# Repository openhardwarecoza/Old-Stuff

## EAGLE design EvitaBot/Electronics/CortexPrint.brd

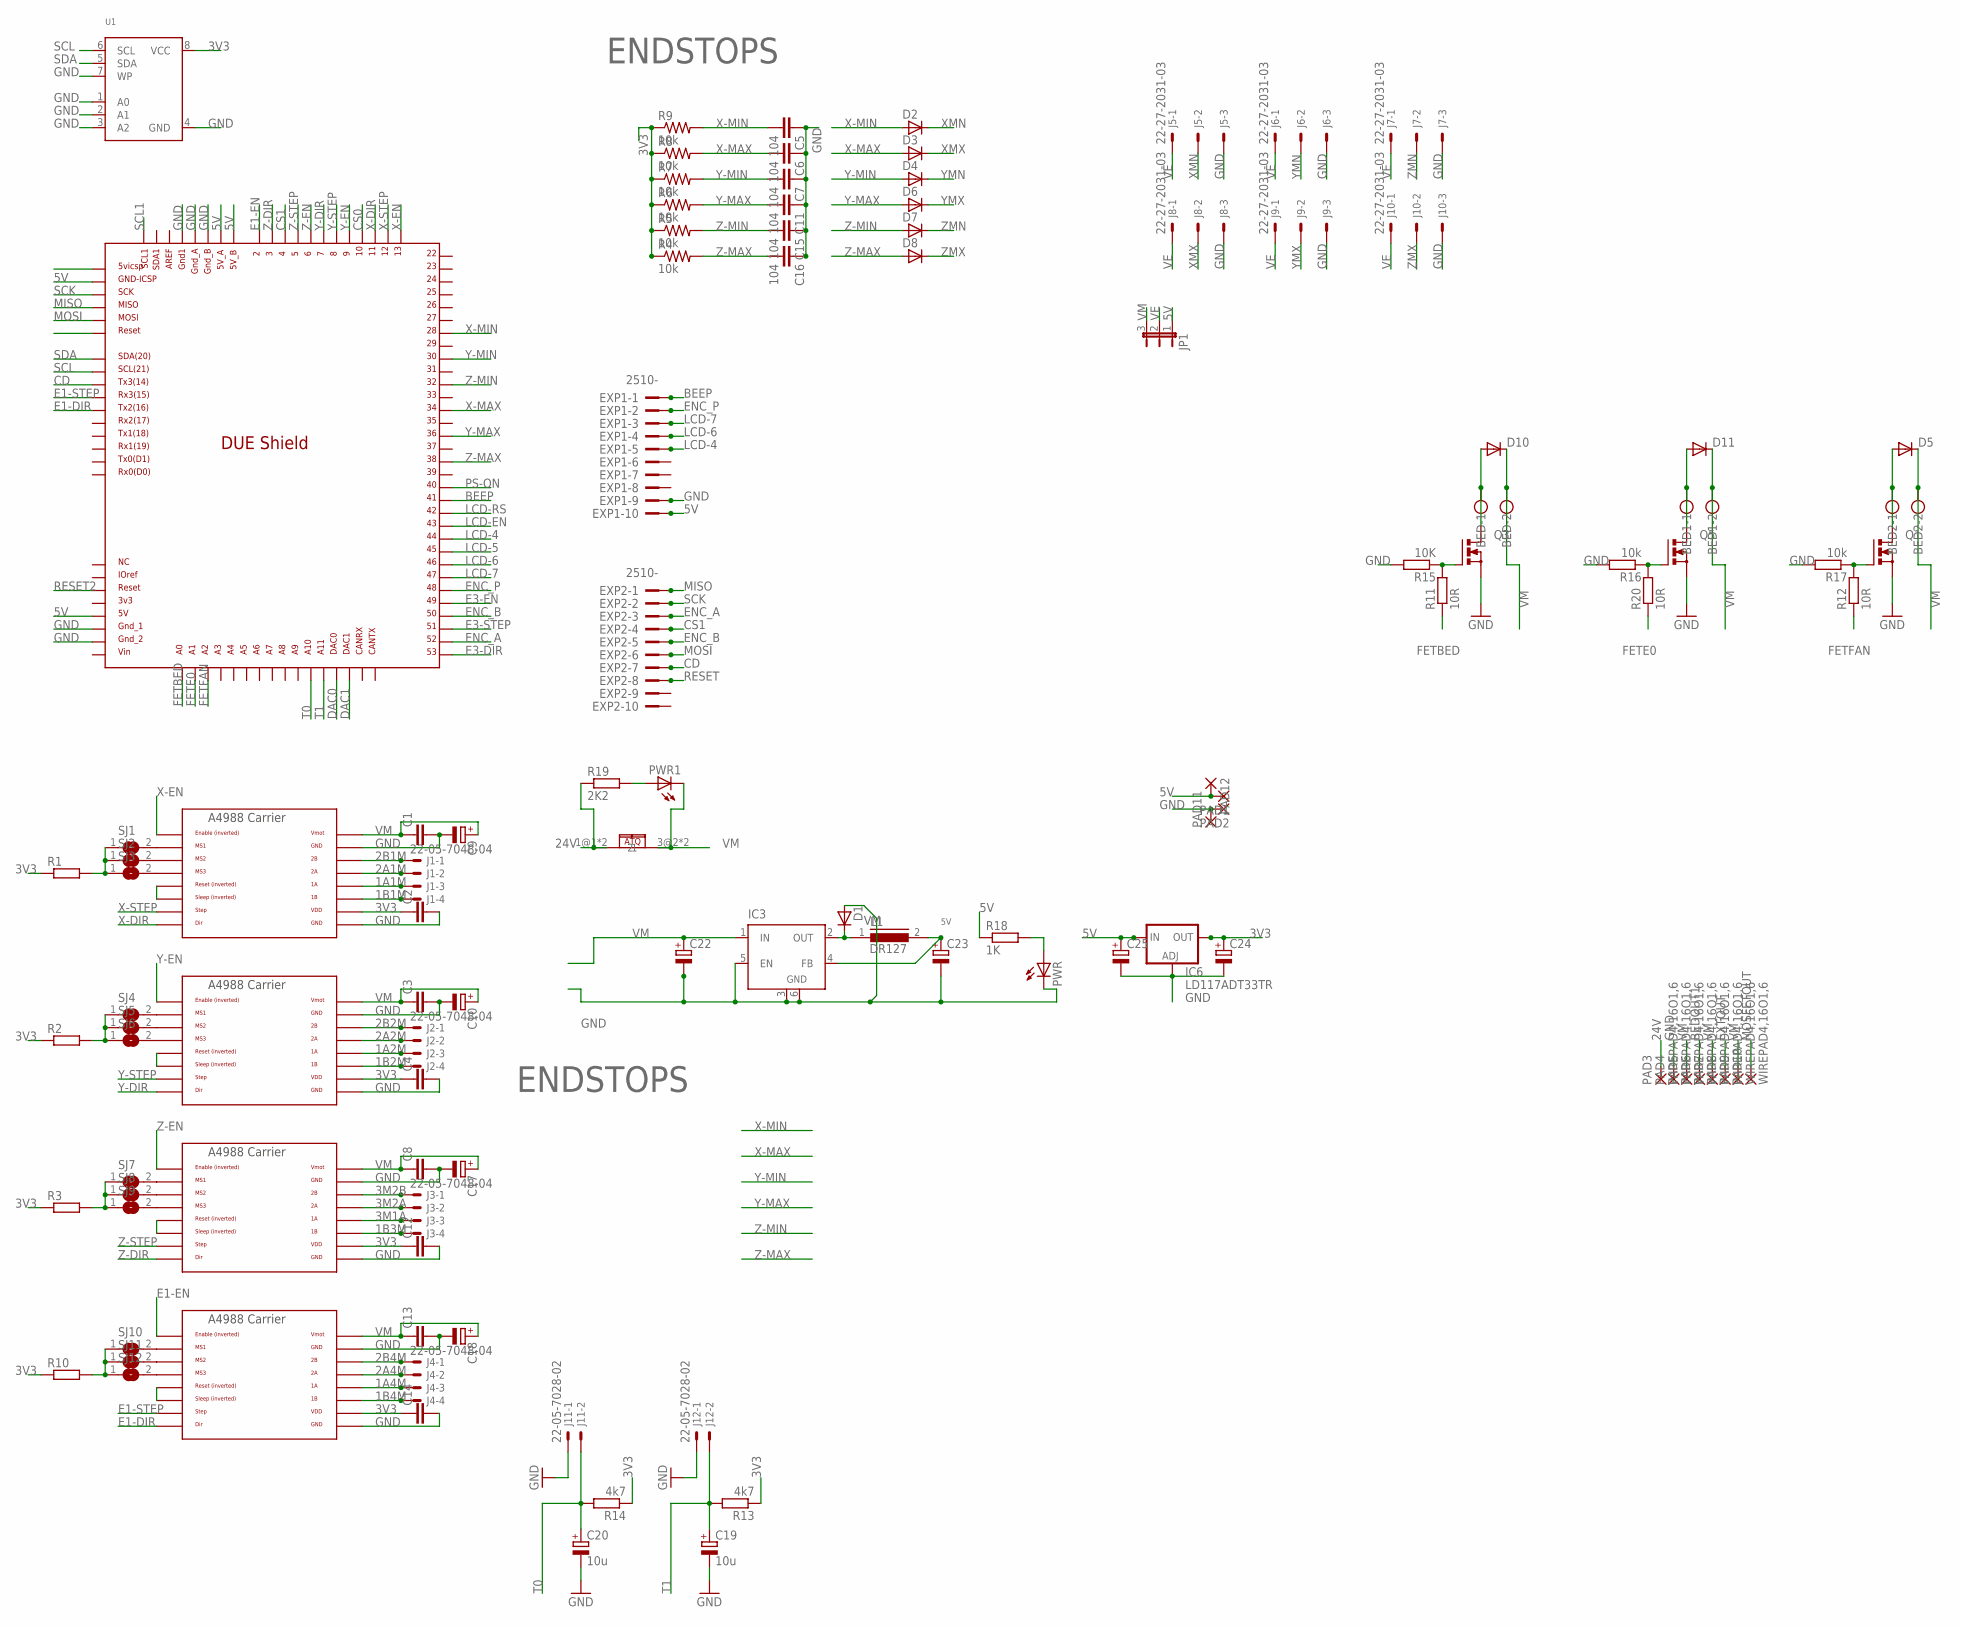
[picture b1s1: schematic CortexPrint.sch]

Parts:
BED, BED1, BED2: W237-102
C1, C2, C3, C4, C8, C12, C13, C14: C-EUC1206; C1206
C5, C6, C7, C11, C15, C16: 104; C1206
C9, C10, C17, C18: CPOL-EUE2,5-6E; E2,5-6E
C19, C20: 10u; SANYO-OSCON_SMD_B6
C22, C23: CPOL-EUE; PANASONIC_E
C24, C25: CPOL-EUD; PANASONIC_D
D1, D2, D3, D4, D6, D7, D8: D-SOD-87; SOD87
D5, D10, D11: DIODESMA-ALT; SMA-DIODE_ALT
EXP1, EXP2: 2510-; PAK100/2500-10
IC3: LM2596S; TO263-5
IC6: LD117ADT33TR; DPACK
J1, J2, J3, J4: 22-05-7048-04; 7395-04
J5, J6, J7, J8, J9, J10: 22-27-2031-03; 6410-03
J11, J12: 22-05-7028-02; 7395-02
JP1: JP2E; JP2
L1: DR127
PAD1, PAD2, PAD11, PAD12: 3,81/1,4
PAD3, PAD4, PAD5, PAD6, PAD7, PAD8, PAD9, PAD10: WIREPAD4,16O1,6; 4,16O1,6
PWR, PWR1: LEDCHIPLED_1206; CHIPLED_1206
Q1, Q3, Q5: PMOSFET_NTO220BV; TO220BV
R1, R3, R10: R-EU_0207/7; 0207/7
R2: R-EU_0204/7; 0204/7
R4, R5, R6, R7, R8, R9, R16, R17: 10k; M1206
R11, R12, R20: 10R; M1206
R13, R14: 4k7; M1206
R15: 10K; M1206
R18: 1K; M1206
R19: 2K2; M1206
SJ1, SJ2, SJ3, SJ4, SJ5, SJ6, SJ7, SJ8, SJ9, SJ10, SJ11, SJ12: SJ
U1: EEPROM_I2C_SOIC8_GENERIC; SOIC8_150MIL
U$1: DUE(NORMAL)
U$2, U$3, U$4, U$5: POLOLU_A4983CARRIER; A4988BREAKOUT
U$7: CQ-121; CQ121

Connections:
1A1M: J1.3, U$2.1A
1A2M: J2.3, U$3.1A
1A4M: J4.3, U$5.1A
1B1M: J1.4, U$2.1B
1B2M: J2.4, U$3.1B
1B3M: J3.4, U$4.1B
1B4M: J4.4, U$5.1B
2A1M: J1.2, U$2.2A
2A2M: J2.2, U$3.2A
2A4M: J4.2, U$5.2A
2B1M: J1.1, U$2.2B
2B2M: J2.1, U$3.2B
2B4M: J4.1, U$5.2B
3M1A: J3.3, U$4.1A
3M2A: J3.2, U$4.2A
3M2B: J3.1, U$4.2B
3V3: C2.1, C4.1, C12.1, C14.1, C24.+, IC6.4 (OUT), R1.1, R2.1, R3.1, R4.1, R5.1, R6.1, R7.1, R8.1, R9.1, R10.1, R13.1, R14.1, U1.8 (VCC), U$2.VDD, U$3.VDD, U$4.VDD, U$5.VDD
5V: C23.+, C25.+, EXP1.10, IC3.4 (FB), IC6.3 (IN), JP1.1, L1.2, PAD1.1, PAD12.1, R18.1, U$1.5V-P (5V), U$1.5V_A, U$1.5V_B, U$1.GND_ICSP
24V: PAD3.1, R19.1, U$7.1@1 (1), U$7.2@1 (1)
BEDOUT1: BED.1, D10.A, PAD6.1, Q3.D
BEEP: EXP1.1, U$1.41
CD: EXP2.7, U$1.TX3
CS0: U$1.10
CS1: EXP2.4, U$1.4
DAC0: U$1.DAC0
DAC1: U$1.DAC1
E1-DIR: U$1.TX2, U$5.DIR
E1-EN: U$1.2, U$5.EN
E1-STEP: U$1.RX3, U$5.STEP
E3-DIR: U$1.53
E3-EN: U$1.49
E3-STEP: U$1.51
ENC_A: EXP2.3, U$1.52
ENC_B: EXP2.5, U$1.50
ENC_P: EXP1.2, U$1.48
EXTOUT: BED1.1, D11.A, PAD8.1, Q5.D
FETBED: R11.1, U$1.A0
FETE0: R20.1, U$1.A1
FETFAN: R12.1, U$1.A2
GND: C1.2, C2.2, C3.2, C4.2, C5.1, C6.1, C7.1, C8.2, C9.-, C10.-, C11.1, C12.2, C13.2, C14.2, C15.1, C16.1, C17.-, C18.-, C19.-, C20.-, C22.-, C23.-, C24.-, C25.-, D1.2 (A), EXP1.9, IC3.3 (GND), IC3.5 (EN), IC3.6 (GND), IC6.1 (ADJ), J5.3, J6.3, J7.3, J8.3, J9.3, J10.3, J11.1, J12.1, PAD2.1, PAD4.1, PAD11.1, PWR.C, Q1.S, Q3.S, Q5.S, R15.2, R16.2, R17.2, U1.1 (A0), U1.2 (A1), U1.3 (A2), U1.4 (GND), U1.7 (WP), U$1.GND1, U$1.GND_1, U$1.GND_2, U$1.GND_A, U$1.GND_B, U$2.GND, U$2.GND@0 (GND), U$3.GND, U$3.GND@0 (GND), U$4.GND, U$4.GND@0 (GND), U$5.GND, U$5.GND@0 (GND)
LCD-4: EXP1.5, U$1.44
LCD-5: U$1.45
LCD-6: EXP1.4, U$1.46
LCD-7: EXP1.3, U$1.47
LCD-EN: U$1.43
LCD-RS: U$1.42
MISO: EXP2.1, U$1.MISO_ICSP
MOSFETOUT: BED2.1, D5.A, PAD10.1, Q1.D
MOSI: EXP2.6, U$1.MOSI_ICSP
unnamed: Q1.G, R12.2, R17.1
unnamed: D1.1 (C), IC3.2 (OUT), L1.1
unnamed: PWR1.A, R19.2
unnamed: U$3.RST, U$3.SLP (SLEEP)
unnamed: SJ4.2, U$3.MS1
unnamed: SJ1.2, U$2.MS1
unnamed: SJ2.2, U$2.MS2
unnamed: SJ3.2, U$2.MS3
unnamed: R1.2, SJ1.1, SJ2.1, SJ3.1
unnamed: SJ5.2, U$3.MS2
unnamed: SJ6.2, U$3.MS3
unnamed: R2.2, SJ4.1, SJ5.1, SJ6.1
unnamed: U$4.RST, U$4.SLP (SLEEP)
unnamed: SJ7.2, U$4.MS1
unnamed: U$2.RST, U$2.SLP (SLEEP)
unnamed: SJ8.2, U$4.MS2
unnamed: SJ9.2, U$4.MS3
unnamed: R3.2, SJ7.1, SJ8.1, SJ9.1
unnamed: U$5.RST, U$5.SLP (SLEEP)
unnamed: SJ10.2, U$5.MS1
unnamed: SJ11.2, U$5.MS2
unnamed: SJ12.2, U$5.MS3
unnamed: R10.2, SJ10.1, SJ11.1, SJ12.1
unnamed: PWR.A, R18.2
unnamed: Q5.G, R16.1, R20.2
unnamed: Q3.G, R11.2, R15.1
PS-ON: U$1.40
RESET: EXP2.8, U$1.RESET_ICSP
RESET2: U$1.RESET
SCK: EXP2.2, U$1.SCK_ICSP
SCL: U1.6 (SCL), U$1.SCL
SCL1: U$1.SCL1
SDA: U1.5 (SDA), U$1.SDA
T0: C20.+, J11.2, R14.2, U$1.A10
T1: C19.+, J12.2, R13.2, U$1.A11
VE: J5.1, J6.1, J7.1, J8.1, J9.1, J10.1, JP1.2
VM: BED.2, BED1.2, BED2.2, C1.1, C3.1, C8.1, C9.+, C10.+, C13.1, C17.+, C18.+, C22.+, D5.C, D10.C, D11.C, IC3.1 (IN), JP1.3, PAD5.1, PAD7.1, PAD9.1, PWR1.C, U$2.VMOT, U$3.VMOT, U$4.VMOT, U$5.VMOT, U$7.3@2 (2), U$7.4@2 (2)
X-DIR: U$1.11, U$2.DIR
X-EN: U$1.13, U$2.EN
X-MAX: C6.2, D3.2 (A), R8.2, U$1.34
X-MIN: C5.2, D2.2 (A), R9.2, U$1.28
X-STEP: U$1.12, U$2.STEP
XMN: D2.1 (C), J5.2
XMX: D3.1 (C), J8.2
Y-DIR: U$1.7, U$3.DIR
Y-EN: U$1.9, U$3.EN
Y-MAX: C11.2, D6.2 (A), R6.2, U$1.36
Y-MIN: C7.2, D4.2 (A), R7.2, U$1.30
Y-STEP: U$1.8, U$3.STEP
YMN: D4.1 (C), J6.2
YMX: D6.1 (C), J9.2
Z-DIR: U$1.3, U$4.DIR
Z-EN: U$1.6, U$4.EN
Z-MAX: C16.2, D8.2 (A), R4.2, U$1.38
Z-MIN: C15.2, D7.2 (A), R5.2, U$1.32
Z-STEP: U$1.5, U$4.STEP
ZMN: D7.1 (C), J7.2
ZMX: D8.1 (C), J10.2

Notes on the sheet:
ENDSTOPS

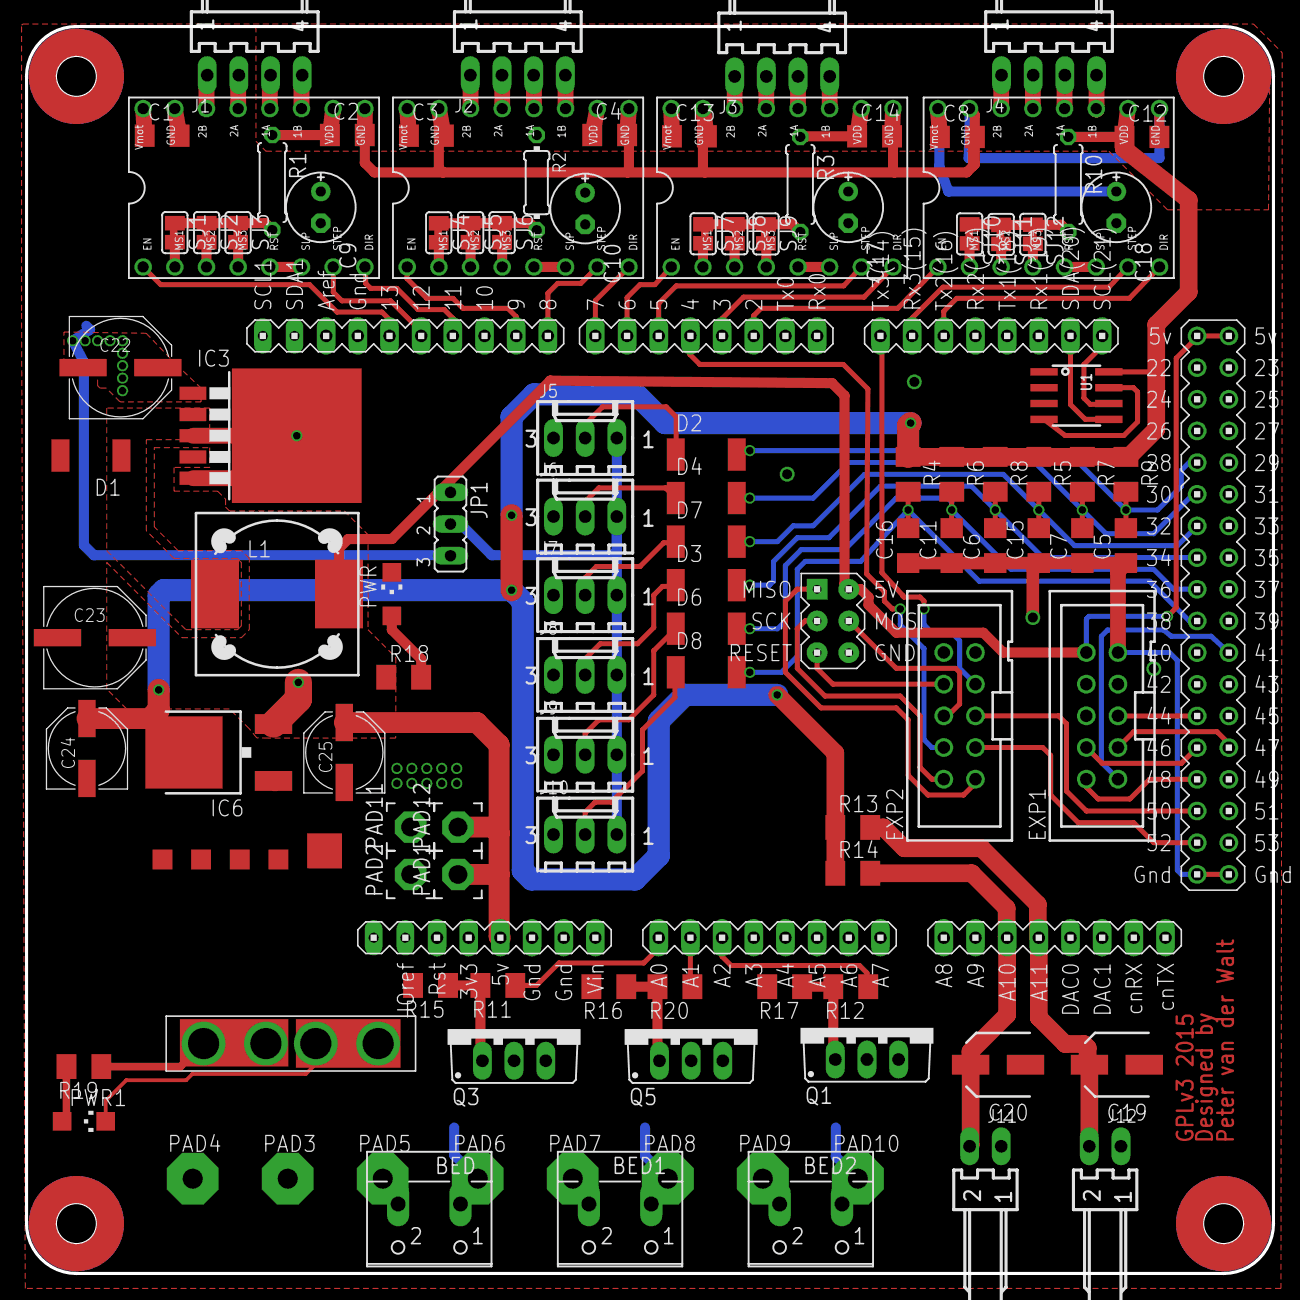
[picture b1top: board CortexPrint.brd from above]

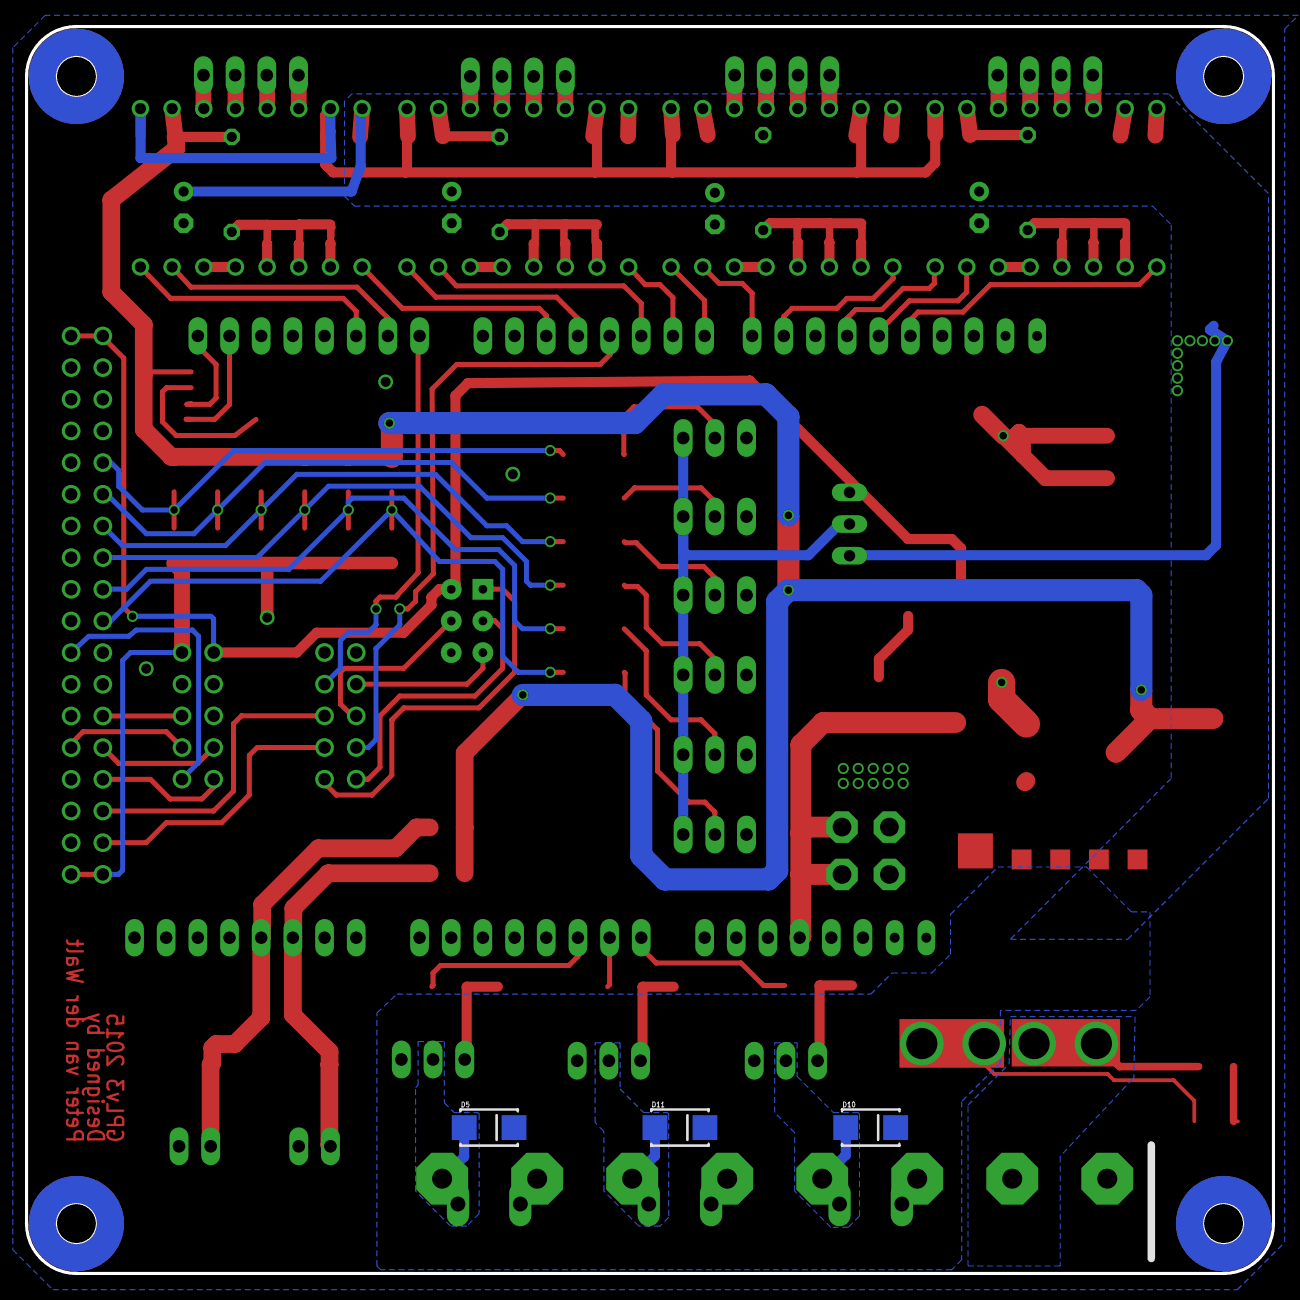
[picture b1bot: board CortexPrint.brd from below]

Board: 2 copper layers, 100.0 x 100.0 mm, 111 parts (3 on the bottom side), 95 nets.

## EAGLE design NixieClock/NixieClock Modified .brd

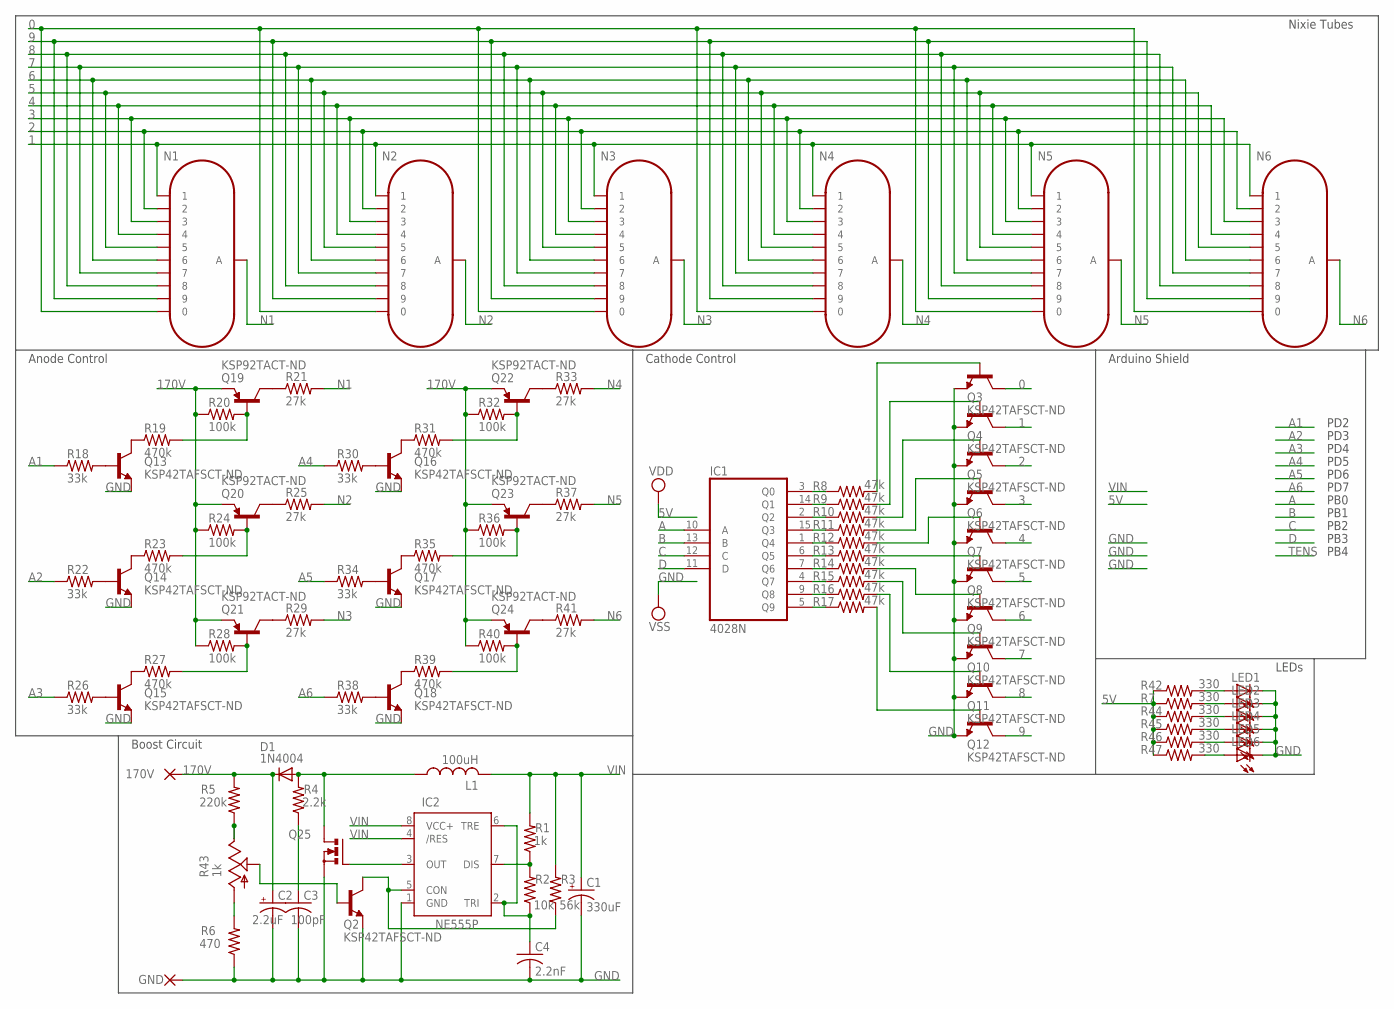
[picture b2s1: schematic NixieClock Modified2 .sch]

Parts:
C1: 330uF; E2,5-6E
C2: 2.2uF; E2,5-6E
C3: 100pF; C050-025X075
C4: 2.2nF; C025-025X050
D1: 1N4004; DO41-10
IC1: 4028N; DIL16
IC2: NE555P; DIL-08
L1: 100uH; 6000-XXXX-RC
LED1, LED2, LED3, LED4, LED5, LED6: LEDCHIPLED_1206; CHIPLED_1206
N1, N2, N3, N4, N5, N6: IN-17
PAD13: GND; 1,6/0,8
PAD14: 170V; 1,6/0,8
Q2, Q3, Q4, Q5, Q6, Q7, Q8, Q9, Q10, Q11, Q12, Q13, Q14, Q15, Q16, Q17, Q18: KSP42TAFSCT-ND; TO-92-AMMO
Q19, Q20, Q21, Q22, Q23, Q24: KSP92TACT-ND; TO-92-AMMO
Q25: PMOSFET_NTO220BH; TO220BH
R1: 1k; 0204/5
R2: 10k; 0204/5
R3: 56k; 0204/5
R4: 2.2k; 0204/5
R5: 220k; 0204/5
R6: 470; 0204/5
R7, R42, R44, R45, R46, R47: 330; 0204/5
R8, R9, R10, R11, R12, R13, R14, R15, R16, R17: 47k; 0204/5
R18, R22, R26, R30, R34, R38: 33k; 0204/5
R19, R23, R27, R31, R35, R39: 470k; 0204/5
R20, R24, R28, R32, R36, R40: 100k; 0204/5
R21, R25, R29, R33, R37, R41: 27k; 0204/5
R43: 1k; B64Y

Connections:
0: N1.0, N2.0, N3.0, N4.0, N5.0, N6.0, Q3.3 (C)
1: N1.1, N2.1, N3.1, N4.1, N5.1, N6.1, Q4.3 (C)
2: N1.2, N2.2, N3.2, N4.2, N5.2, N6.2, Q5.3 (C)
3: N1.3, N2.3, N3.3, N4.3, N5.3, N6.3, Q6.3 (C)
4: N1.4, N2.4, N3.4, N4.4, N5.4, N6.4, Q7.3 (C)
5: N1.5, N2.5, N3.5, N4.5, N5.5, N6.5, Q8.3 (C)
5V: IC1.16 (VDD), R7.1, R42.1, R44.1, R45.1, R46.1, R47.1
6: N1.6, N2.6, N3.6, N4.6, N5.6, N6.6, Q9.3 (C)
7: N1.7, N2.7, N3.7, N4.7, N5.7, N6.7, Q10.3 (C)
8: N1.8, N2.8, N3.8, N4.8, N5.8, N6.8, Q11.3 (C)
9: N1.9, N2.9, N3.9, N4.9, N5.9, N6.9, Q12.3 (C)
170V: C2.+, D1.C, PAD14.1, Q19.1 (E), Q20.1 (E), Q21.1 (E), Q22.1 (E), Q23.1 (E), Q24.1 (E), R5.2, R20.1, R24.1, R28.1, R32.1, R36.1, R40.1
A: IC1.10 (A)
A1: R18.1
A2: R22.1
A3: R26.1
A4: R30.1
A5: R34.1
A6: R38.1
B: IC1.13 (B)
C: IC1.12 (C)
D: IC1.11 (D)
GND: C1.-, C2.-, C3.2, C4.2, IC1.8 (VSS), IC2.1 (GND), LED1.C, LED2.C, LED3.C, LED4.C, LED5.C, LED6.C, PAD13.1, Q2.1 (E), Q3.1 (E), Q4.1 (E), Q5.1 (E), Q6.1 (E), Q7.1 (E), Q8.1 (E), Q9.1 (E), Q10.1 (E), Q11.1 (E), Q12.1 (E), Q13.1 (E), Q14.1 (E), Q15.1 (E), Q16.1 (E), Q17.1 (E), Q18.1 (E), Q25.S, R6.1
N1: N1.A, R21.2
N2: N2.A, R25.2
N3: N3.A, R29.2
N4: N4.A, R33.2
N5: N5.A, R37.2
N6: N6.A, R41.2
unnamed: IC2.3 (OUT), Q25.G
unnamed: IC2.7 (DIS), R1.1, R2.2
unnamed: C4.1, IC2.2 (TRI), IC2.6 (TRE), R2.1
unnamed: IC2.5 (CON), Q2.3 (C), R3.1
unnamed: C3.1, R4.1
unnamed: D1.A, L1.1, Q25.D, R4.2
unnamed: Q13.2 (B), R18.2
unnamed: R6.2, R43.A
unnamed: R5.1, R43.E
unnamed: Q2.2 (B), R43.S
unnamed: IC1.3 (Q0), R8.1
unnamed: IC1.14 (Q1), R9.1
unnamed: IC1.2 (Q2), R10.1
unnamed: IC1.15 (Q3), R11.1
unnamed: IC1.1 (Q4), R12.1
unnamed: IC1.6 (Q5), R13.1
unnamed: IC1.7 (Q6), R14.1
unnamed: IC1.4 (Q7), R15.1
unnamed: IC1.9 (Q8), R16.1
unnamed: Q13.3 (C), R19.1
unnamed: IC1.5 (Q9), R17.1
unnamed: Q3.2 (B), R8.2
unnamed: Q4.2 (B), R9.2
unnamed: Q5.2 (B), R10.2
unnamed: Q6.2 (B), R11.2
unnamed: Q12.2 (B), R17.2
unnamed: Q19.3 (C), R21.1
unnamed: Q19.2 (B), R19.2, R20.2
unnamed: Q10.2 (B), R15.2
unnamed: Q9.2 (B), R14.2
unnamed: Q8.2 (B), R13.2
unnamed: Q14.2 (B), R22.2
unnamed: Q14.3 (C), R23.1
unnamed: Q20.3 (C), R25.1
unnamed: Q20.2 (B), R23.2, R24.2
unnamed: Q15.2 (B), R26.2
unnamed: Q15.3 (C), R27.1
unnamed: Q21.3 (C), R29.1
unnamed: Q21.2 (B), R27.2, R28.2
unnamed: Q16.2 (B), R30.2
unnamed: Q16.3 (C), R31.1
unnamed: Q22.3 (C), R33.1
unnamed: Q22.2 (B), R31.2, R32.2
unnamed: Q17.2 (B), R34.2
unnamed: Q17.3 (C), R35.1
unnamed: Q23.3 (C), R37.1
unnamed: Q23.2 (B), R35.2, R36.2
unnamed: Q18.2 (B), R38.2
unnamed: Q18.3 (C), R39.1
unnamed: Q24.3 (C), R41.1
unnamed: Q24.2 (B), R39.2, R40.2
unnamed: LED1.A, R42.2
unnamed: LED2.A, R7.2
unnamed: LED3.A, R44.2
unnamed: Q11.2 (B), R16.2
unnamed: Q7.2 (B), R12.2
unnamed: LED4.A, R45.2
unnamed: LED5.A, R46.2
unnamed: LED6.A, R47.2
VIN: C1.+, IC2.4 (/RES), IC2.8 (VCC+), L1.2, R1.2, R3.2

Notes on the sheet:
PD2
PD3
PD4
PD5
PD6
PD7
PB0
PB1
PB2
PB3
PB4
Nixie Tubes
Anode Control
Cathode Control
Arduino Shield
LEDs
Boost Circuit

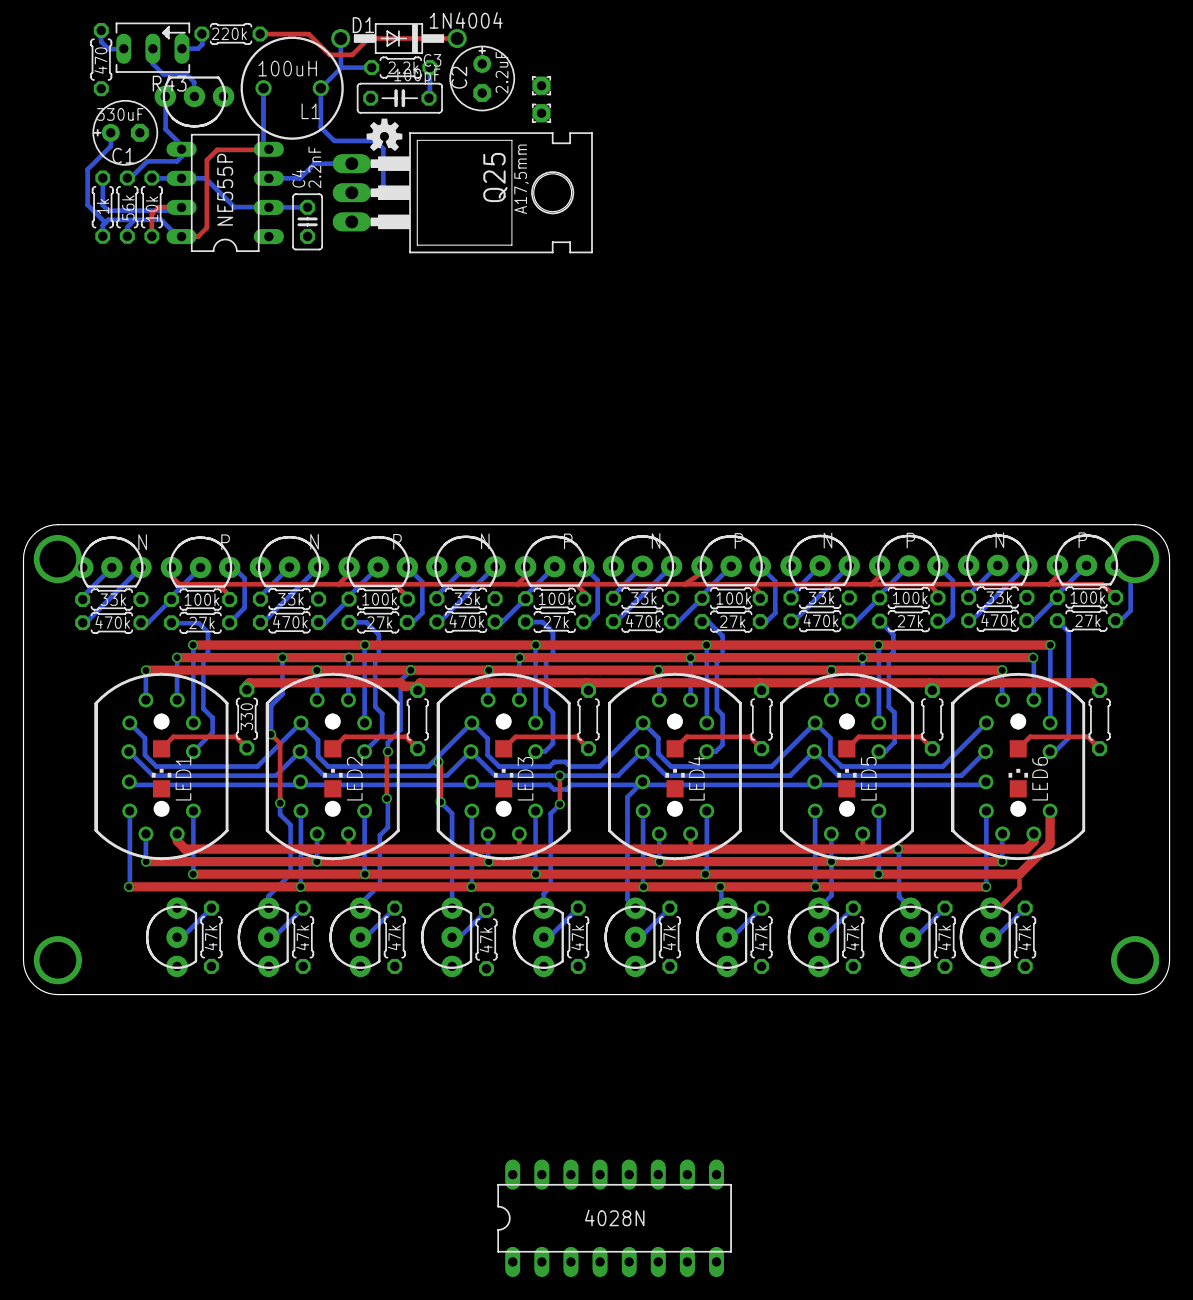
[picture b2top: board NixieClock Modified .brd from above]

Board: 2 copper layers, 100.0 x 41.0 mm, 94 parts (0 on the bottom side), 79 nets.

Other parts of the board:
U$7: OSHW-LOGO-S

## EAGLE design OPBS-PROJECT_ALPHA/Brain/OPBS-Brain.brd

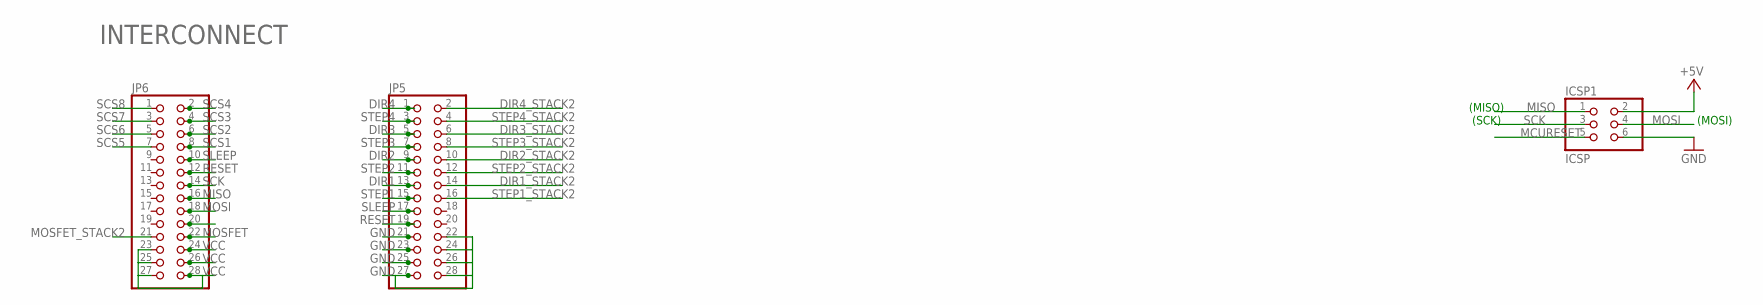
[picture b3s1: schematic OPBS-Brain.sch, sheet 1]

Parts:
ICSP1: ICSP; 2X03
JP5, JP6: PINHD-2X14; 2X14

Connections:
DIR1: JP5.13
DIR1_STACK2: JP5.14
DIR2: JP5.9
DIR2_STACK2: JP5.10
DIR3: JP5.5
DIR3_STACK2: JP5.6
DIR4: JP5.1
DIR4_STACK2: JP5.2
GND: ICSP1.6, JP5.21, JP5.22, JP5.23, JP5.24, JP5.25, JP5.26, JP5.27, JP5.28; also elsewhere on the board
MCURESET: ICSP1.5
MISO: ICSP1.1, JP6.16
MOSFET: JP6.22
MOSFET_STACK2: JP6.21
MOSI: ICSP1.4, JP6.18
PULLUPVCC: JP6.20
RESET: JP5.19, JP6.12
SCK: ICSP1.3, JP6.14
SCS1: JP6.8
SCS2: JP6.6
SCS3: JP6.4
SCS4: JP6.2
SCS5: JP6.7
SCS6: JP6.5
SCS7: JP6.3
SCS8: JP6.1
SLEEP: JP5.17, JP6.10
STEP1: JP5.15
STEP1_STACK2: JP5.16
STEP2: JP5.11
STEP2_STACK2: JP5.12
STEP3: JP5.7
STEP3_STACK2: JP5.8
STEP4: JP5.3
STEP4_STACK2: JP5.4
VCC: ICSP1.2, JP6.23, JP6.24, JP6.25, JP6.26, JP6.27, JP6.28; also elsewhere on the board

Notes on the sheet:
INTERCONNECT
(SCK)
(MISO)
(MOSI)

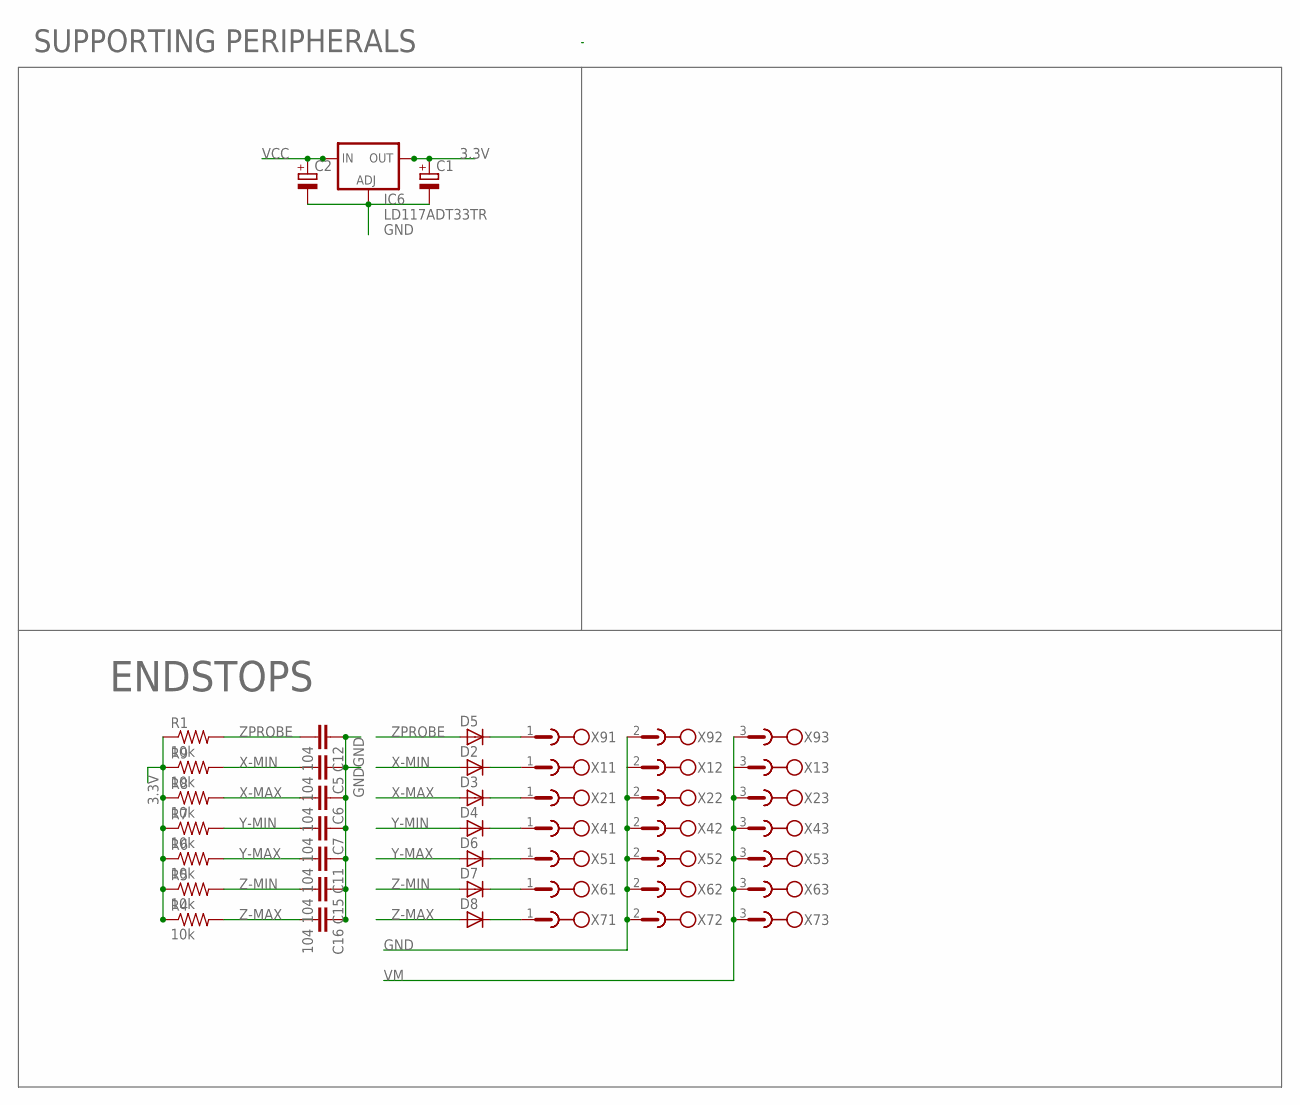
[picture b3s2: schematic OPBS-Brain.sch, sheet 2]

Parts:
C1, C2: CPOL-EUE; PANASONIC_E
C5, C6, C7, C11, C12, C15, C16: 104; C1206
D2, D3, D4, D5, D6, D7, D8: D-SOD-87; SOD87
IC6: LD117ADT33TR; DPACK
R1, R4, R5, R6, R7, R8, R9: 10k; M1206
X1, X2, X4, X5, X6, X7, X9: MC1.5/3; MC1.5/3-G-3.81

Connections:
3.3V: C1.+, IC6.4 (OUT), R1.1, R4.1, R5.1, R6.1, R7.1, R8.1, R9.1
GND: C1.-, C2.-, C5.1, C6.1, C7.1, C11.1, C12.1, C15.1, C16.1, IC6.1 (ADJ), X1.2, X2.2, X4.2, X5.2, X6.2, X7.2, X9.2; also elsewhere on the board
unnamed: D2.1 (C), X1.1
unnamed: D3.1 (C), X2.1
unnamed: D4.1 (C), X4.1
unnamed: D6.1 (C), X5.1
unnamed: D7.1 (C), X6.1
unnamed: D8.1 (C), X7.1
VCC: C2.+, IC6.3 (IN); also elsewhere on the board
VM: X1.3, X2.3, X4.3, X5.3, X6.3, X7.3, X9.3
X-MAX: C6.2, D3.2 (A), R8.2
X-MIN: C5.2, D2.2 (A), R9.2
Y-MAX: C11.2, D6.2 (A), R6.2
Y-MIN: C7.2, D4.2 (A), R7.2
Z-MAX: C16.2, D8.2 (A), R4.2
Z-MIN: C15.2, D7.2 (A), R5.2
Z-PROBE-HIVOLT: D5.1 (C), X9.1
ZPROBE: C12.2, D5.2 (A), R1.2

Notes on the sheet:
ENDSTOPS
SUPPORTING PERIPHERALS

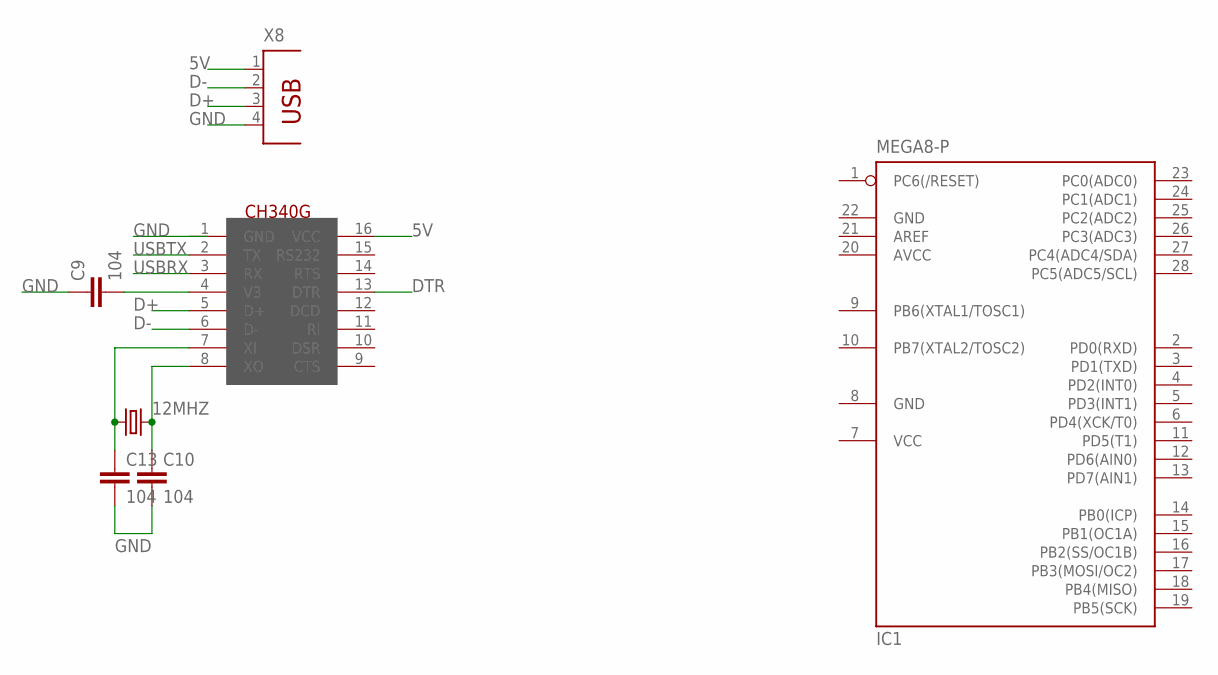
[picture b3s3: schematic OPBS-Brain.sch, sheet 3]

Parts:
12MHZ: CRYSTALHC49UP; HC49UP@1
C9, C10, C13: 104; C1206
IC1: MEGA8-P; DIL28-3
U$1: CH340G; SOIC16
X8: PN61729

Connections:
5V: U$1.16 (VCC), X8.1
AVCC: IC1.20 (AVCC)
D+: U$1.5 (D+), X8.3
D-: U$1.6 (D-), X8.2
DTR: U$1.13 (DTR)
GND: C9.1, C10.2, C13.2, IC1.8 (GND), IC1.22 (GND), X8.4; also elsewhere on the board
unnamed: 12MHZ.1, C13.1, U$1.7 (XI)
unnamed: 12MHZ.2, C10.1, U$1.8 (XO)
unnamed: C9.2, U$1.4 (V3)
USBRX: U$1.3 (RX)
USBTX: U$1.2 (TX)
VCC: IC1.7 (VCC); also elsewhere on the board

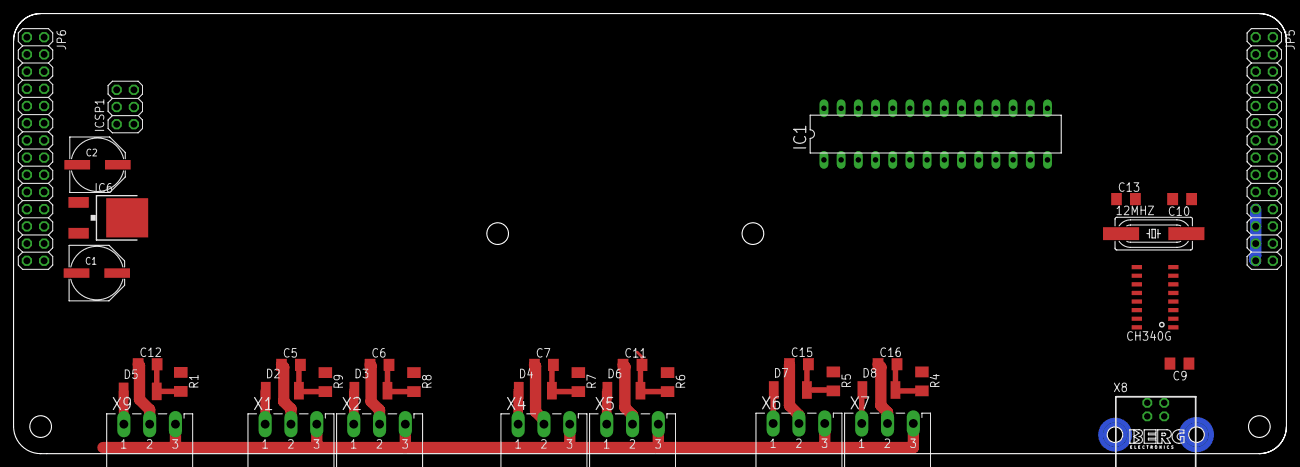
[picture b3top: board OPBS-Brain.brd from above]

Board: 2 copper layers, 188.0 x 65.0 mm, 41 parts (0 on the bottom side), 29 nets.

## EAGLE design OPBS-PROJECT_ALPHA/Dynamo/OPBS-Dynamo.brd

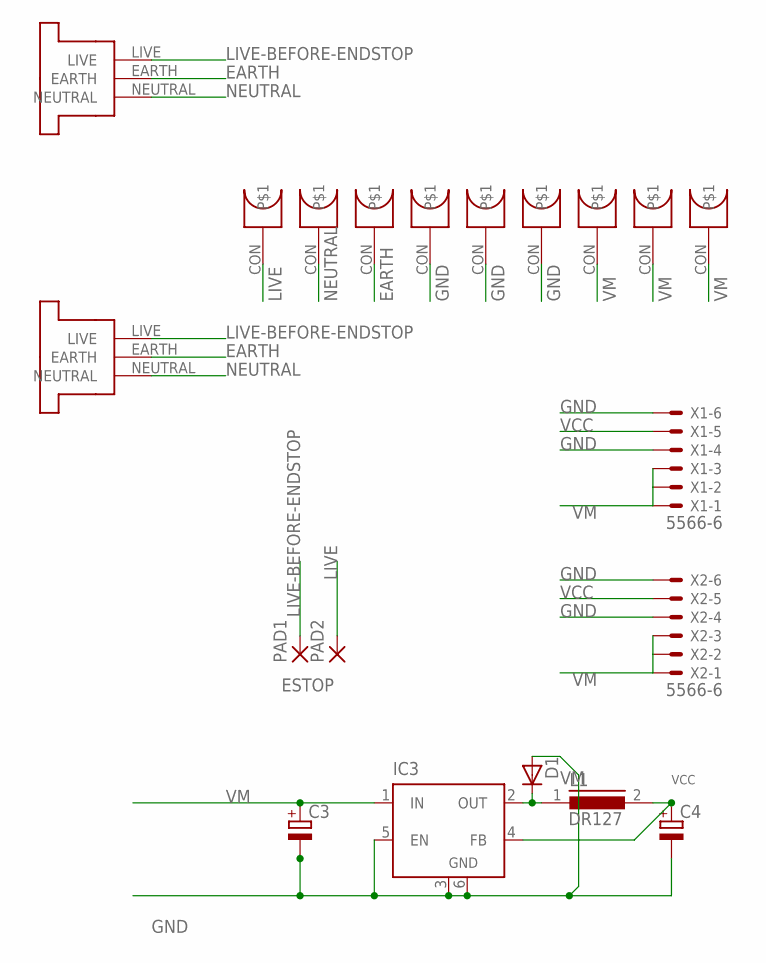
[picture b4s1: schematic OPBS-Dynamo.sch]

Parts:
C3, C4: CPOL-EUE; PANASONIC_E
D1: D-SOD-87; SOD87
EARTH: SLIDEINSCREW9.53; SLIDEINSCREW
GND1, GND2, GND3: SLIDEINSCREW9.53; SLIDEINSCREW
IC3: LM2596S; TO263-5
L1: DR127
LIVE: SLIDEINSCREW9.53; SLIDEINSCREW
NEUTRAL: SLIDEINSCREW9.53; SLIDEINSCREW
PAD1, PAD2: 3,81/1,4
U$1, U$2: IEC320JR-101S; IEC320-JR101S
V1, V2, V3: SLIDEINSCREW9.53; SLIDEINSCREW
X1, X2: 5566-6

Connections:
EARTH: EARTH.CON, U$1.EARTH, U$2.EARTH
GND: C3.-, C4.-, D1.2 (A), GND1.CON, GND2.CON, GND3.CON, IC3.3 (GND), IC3.5 (EN), IC3.6 (GND), X1.4, X1.6, X2.4, X2.6
LIVE: LIVE.CON, PAD2.1
LIVE-BEFORE-ENDSTOP: PAD1.1, U$1.LIVE, U$2.LIVE
unnamed: D1.1 (C), IC3.2 (OUT), L1.1
NEUTRAL: NEUTRAL.CON, U$1.NEUTRAL, U$2.NEUTRAL
VCC: C4.+, IC3.4 (FB), L1.2, X1.5, X2.5
VM: C3.+, IC3.1 (IN), V1.CON, V2.CON, V3.CON, X1.1, X1.2, X1.3, X2.1, X2.2, X2.3

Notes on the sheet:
ESTOP

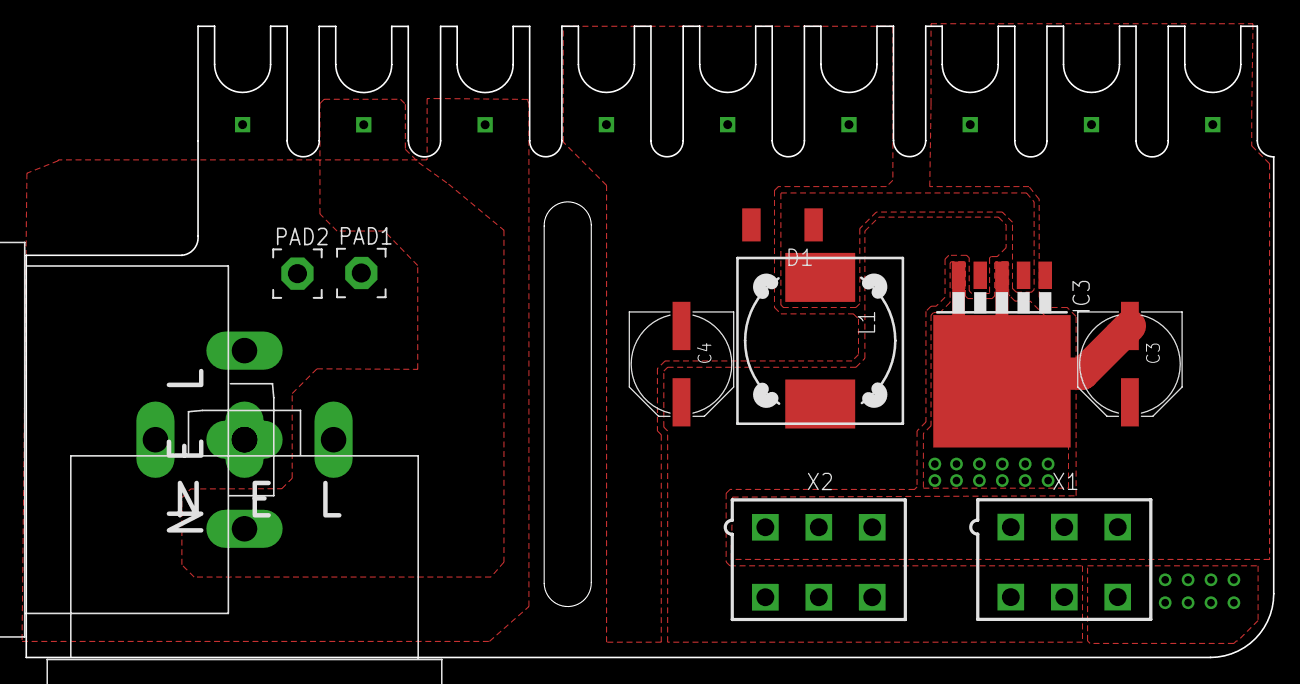
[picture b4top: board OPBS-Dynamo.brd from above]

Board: 2 copper layers, 98.0 x 49.6 mm, 20 parts (0 on the bottom side), 8 nets.

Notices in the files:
EvitaBot/Electronics/CortexPrint.brd:
GPLv3 2015
parts and their libraries:
SparkFun-DiscreteSemi: Licensing: CC v3.0 Share-Alike You are welcome to use this library for commercial purposes.
microbuilder: This work is placed in the public domain, and may be freely used for commercial and non-commercial work with the following conditions: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
02_eigene: Konrad Meyer (c) 2011
